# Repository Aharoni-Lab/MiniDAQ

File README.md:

# MiniDAQ
Simplified DAQ for Miniscopes and Minicams. This is effectively a smaller version of the [standard Miniscope DAQ](https://github.com/daharoni/Miniscope_DAQ_PCB) and does not include easily accessible trigger and sync connections but should support all other functionality of the Miniscope platform.

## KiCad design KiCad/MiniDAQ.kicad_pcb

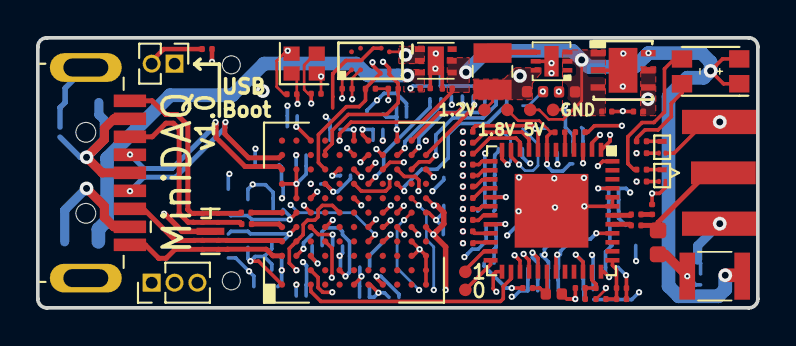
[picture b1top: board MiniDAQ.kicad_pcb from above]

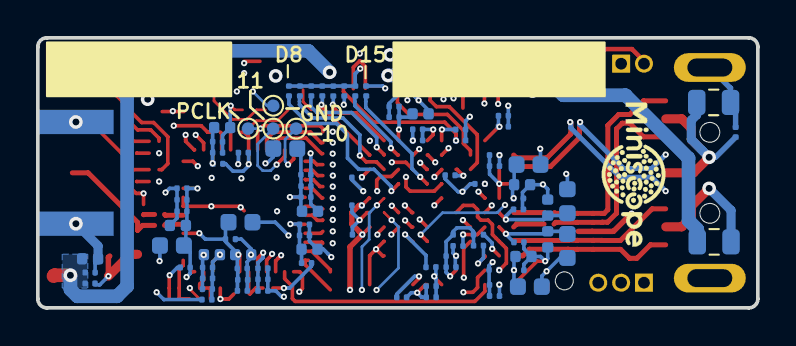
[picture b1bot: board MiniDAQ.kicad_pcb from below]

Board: 6 copper layers, 40.0 x 15.0 mm, 161 parts (93 on the bottom side), 96 nets.

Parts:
C1, C6, C9, C13, C14, C18, C19, C24, C25, C29, C38, C42, C49, C54, C60, C64, C66, C69, C71: 10nF; C_0201_0603Metric_L
C2, C5, C7, C10, C12, C15, C20, C23, C26, C30, C35, C37, C39, C40, C41, C43, C45, C46, C48, C50, C51, C53, C57, C58, C59, C61, C63, C65, C67, C68, C70, C72, C74: 0.1uF; C_0201_0603Metric_L
C3, C8, C11: 4.7uF; C_0402_1005Metric_L
C4, C22, C28, C32, C73, C75: 10uF; C_0402_1005Metric_L
C16, C21, C27, C31, C33, C34, C77, C78: 1uF; C_0201_0603Metric_L
C17: 47nF; C_0201_0603Metric_L
C36, C47, C52: 2.2uF; C_0402_1005Metric_L
C44, C62, C76: 22uF; C_0402_1005Metric_L
C55, C56: 12pF; C_0201_0603Metric_L
C79: 0 Res; C_0201_0603Metric_L
D1: LTST-C155GEKT; LED_4_P138_270X320X110L50X90N
J1: USB3_A; USB3_A_Plug_Wuerth_692112030100_Horizontal
J2: SMA-J-P-H-ST-EM1; SMA_Samtec_SMA-J-P-H-ST-EM1_EdgeMount
J3, J4, J5, J6: Conn_01x01; Conn_1x1_700_Circular_Pad
J7: Conn_01x03; PinHeader_1x03_P1.27mm_Vertical
JP1: Jumper_2_Open; PinHeader_1x02_P1.27mm_Vertical
J_NA: Conn_01x01; Conn_1x1_700_Circular_Pad
J_NA#2, J_NA#3, J_NA#4, J_NA#5, J_NA#6, J_NA#7, J_NA#8: Conn_01x01; Conn_1x1_700_Circular_Pad
L1, L2, L3, L5, L6, L8, L9, L10: BLM18PG471SN1D; L_0603_1608Metric_L
L4, L7: BLM21PG221SN1D; L_0805_2012Metric
L11: ADL3225V-470MT-TL000; L_1210_3225Metric_L
L12: LQM2HPN1R0MG0; L_1008_2520Metric_L
Q1, Q2: MMBT3904LP-7B; TRXDFN3_101X61X53L25X15N
R1, R2, R3, R9, R14, R15, R29, R43: 10K; R_0201_0603Metric_ERJ_L
R4, R6: 10K 1%; R_0201_0603Metric_ERJ_L
R5, R8: 0 1%; R_0201_0603Metric_ERJ_L
R7: 50; R_0201_0603Metric_ERJ_L
R10, R11: 2k; R_0201_0603Metric_ERJ_L
R12: 200 1%; R_0201_0603Metric_ERJ_L
R13: 6.04K 1%; R_0201_0603Metric_ERJ_L
R16, R17, R18, R19, R20, R21, R22, R23, R26, R27, R28, R33, R34, R35, R36, R37, R38, R39, R40: 22; R_0201_0603Metric_ERJ_L
R24, R25, R30, R31, R32: 2K; R_0201_0603Metric_ERJ_L
R41, R42: 0; R_0201_0603Metric_ERJ_L
U1: DS90UB934-Q1; QFN_49_P50_700X700X100L40X24T410N
U2: NCP360; SON7P65_200X200X55L30X30T160X90L
U3: SP3010-04UTG; uDFN-10
U4: CYUSB3014; BGA121CP80_11X11_1000X1000X120B30
U5: M24M02-R
U6: SC189CULTRT; SON_7P50_200X200X57L35X24T170X80N
U7: NCP692MN18T2G; NCP692MN50T2G
Y1: SMD_CRYSTAL; Crystal_SMD_2016-4Pin_2.0x1.6mm

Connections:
+1V2: C62.1, C63.1, C64.1, C65.1, C66.1, C67.1, C68.1, C69.1, C70.1, C71.1, C72.1, C76.1, J_NA#6.1, L5.1, L6.1, L8.1, L12.2, U4.B10, U4.C3, U4.E9, U4.F11, U4.H1, U4.J11, U4.L5, U4.L7, U6.6
+1V8: C13.2, C14.2, C15.2, C16.2, C37.1, C38.1, C41.1, C42.1, C48.1, C49.1, C53.1, C54.1, C58.1, C59.1, C60.1, C61.1, C78.1, J_NA#5.1, L1.1, L2.1, L3.1, L9.1, R1.1, R2.1, R3.1, R9.2, R14.1, R24.1, R25.1, R29.1, R40.1, R41.2, R42.2, R43.1, U1.7, U1.29, U4.B1, U4.C11, U4.E3, U4.F1, U4.H11, U4.L9, U5.A2, U7.4, U7.5
+5V: C34.1, C50.1, C73.1, C74.1, C75.1, C77.1, D1.1, D1.2, J_NA#3.1, L11.2, R30.2, U2.4, U2.5, U4.E11, U6.2, U6.3, U7.1, U7.3, U7.6
/Deserializer/COAX+: C12.2, J2.1, L10.1
/Deserializer/GPIO0: U1.28, U4.D4
/Deserializer/GPIO1: U1.27, U4.D5
/Deserializer/GPIO2: U1.26, U4.C1
/Deserializer/GPIO3: U1.25, U4.C2
/Deserializer/HSYNC: R27.1, U1.10
/Deserializer/I2C_SCL: R24.2, U1.2, U4.D9, U5.C1
/Deserializer/I2C_SDA: R25.2, U1.1, U4.D10, U5.D2
/Deserializer/IDX: C23.2, R6.2, R8.1, U1.35
/Deserializer/LOCK: U1.48, U4.K5
/Deserializer/MODE: C5.2, R4.2, R5.1, U1.37
/Deserializer/OEN: R2.2, U1.5
/Deserializer/OSS_SEL: R3.2, U1.4
/Deserializer/PCLK: J5.1, R26.1, U1.8
/Deserializer/PDB: C4.2, R1.2, U1.30
/Deserializer/ROUT0: J_NA#7.1, U1.24
/Deserializer/ROUT1: J_NA#8.1, U1.23
/Deserializer/ROUT2: R16.1, U1.22
/Deserializer/ROUT3: R17.1, U1.21
/Deserializer/ROUT4: R18.1, U1.19
/Deserializer/ROUT5: R19.1, U1.18
/Deserializer/ROUT6: R20.1, U1.16
/Deserializer/ROUT7: R21.1, U1.15
/Deserializer/ROUT8: R22.1, U1.14
/Deserializer/ROUT9: R23.1, U1.13
/Deserializer/ROUT10: J3.1, U1.12
/Deserializer/ROUT11: J4.1, U1.11
/Deserializer/VDD11_D: C6.2, C7.2, C8.2, R41.1, U1.3
/Deserializer/VDD11_DVP: C9.2, C10.2, C11.2, R42.1, U1.20
/Deserializer/VDD11_FPD: C1.2, C2.2, C3.2, C79.2, R9.1, U1.34
/Deserializer/VDD18: C29.2, C30.2, C31.2, C32.2, L3.2, R4.1, R6.1, U1.17
/Deserializer/VDD18_FPD0: C24.2, C25.2, C26.2, C27.2, C28.2, L2.2, U1.31, U1.40
/Deserializer/VDD18_P0: C18.2, C19.2, C20.2, C21.2, C22.2, L1.2, U1.36, U1.45
/Deserializer/VSYNC: R28.1, U1.9
/USB/AVDD: C35.1, C36.1, L5.2, U4.A7
/USB/CVDDQ: C51.1, C52.1, L9.2, U4.B6
/USB/FSLC0: R15.1, U4.B2, U4.B4, U4.E6
/USB/GPIO1: J7.2, U4.K7
/USB/GPIO2: J7.3, U4.K6
/USB/LOCK_OUT: R32.2, U4.H6
/USB/PMODE0: JP1.1, U4.G4
/USB/PMODE1: R29.2, U4.H4
/USB/RESET_IN: C57.1, R14.2, U4.C5
/USB/SSD_N: J1.2, U4.A10
/USB/SSD_P: J1.3, U4.A9
/USB/SS_RX_N: J1.8, U3.4, U3.7, U4.A4
/USB/SS_RX_P: J1.9, U3.5, U3.6, U4.A3
/USB/SS_TX_N: C39.2, J1.5, U3.1, U3.10
/USB/SS_TX_P: C40.2, J1.6, U3.2, U3.9
/USB/STATUS: R31.2, U4.G5
/USB/TX_N: C39.1, U4.A6
/USB/TX_P: C40.1, U4.A5
/USB/U3RXVDDQ: C43.1, C44.1, L6.2, U4.A2
/USB/U3TXVDDQ: C46.1, C47.1, L8.2, U4.B5
/USB/XTAL_IN: C56.1, U4.C6, Y1.1
/USB/XTAL_OUT: C55.1, U4.C7, Y1.3
GND: C1.1, C2.1, C3.1, C4.1, C5.1, C6.1, C7.1, C8.1, C9.1, C10.1, C11.1, C13.1, C14.1, C15.1, C16.1, C18.1, C19.1, C20.1, C21.1, C22.1, C23.1, C24.1, C25.1, C26.1, C27.1, C28.1, C29.1, C30.1, C31.1, C32.1, C33.2, C34.2, C35.2, C36.2, C37.2, C38.2, C41.2, C42.2, C43.2, C44.2, C45.1, C46.2, C47.2, C48.2, C49.2, C50.2, C51.2, C52.2, C53.2, C54.2, C55.2, C56.2, C57.2, C58.2, C59.2, C60.2, C61.2, C62.2, C63.2, C64.2, C65.2, C66.2, C67.2, C68.2, C69.2, C70.2, C71.2, C72.2, C73.2, C74.2, C75.2, C76.2, C77.2, C78.2, C79.1, J1.4, J1.7, J2.2, J6.1, J7.1, J_NA#4.1, L7.2, Q1.2, Q2.2, R5.2, R7.2, R8.2, R12.2, R13.2, R15.2, R33.1, R34.1, R35.1, R36.1, R37.1, R38.1, R39.1, U1.43, U1.44, U1.49, U2.1, U2.2, U2.7, U3.3, U3.8, U4.A1, U4.A8, U4.B7, U4.B8, U4.B9, U4.D8, U4.E2, U4.G1, U4.G11, U4.K3, U4.K4, U4.L1, U4.L2, U4.L3, U4.L6, U4.L11, U5.B2, U5.D3, U6.5, U6.7, U7.2, U7.7, Y1.2, Y1.4
unnamed: C12.1, U1.41
unnamed: C17.1, U1.42
unnamed: C17.2, R7.1
unnamed: C33.1, L4.2, U2.3
unnamed: C45.2, J1.10, L7.1
unnamed: D1.3, R11.1
unnamed: D1.4, R10.1
unnamed: J1.1, L4.1
unnamed: JP1.2, R43.2
unnamed: L10.2, L11.1, R30.1
unnamed: L12.1, U6.4
unnamed: Q1.1, R31.1
unnamed: Q1.3, R10.2
unnamed: Q2.1, R32.1
unnamed: Q2.3, R11.2
unnamed: R12.1, U4.B3
unnamed: R13.1, U4.C8
unnamed: R16.2, U4.F10
unnamed: R17.2, U4.F9
unnamed: R18.2, U4.F7
unnamed: R19.2, U4.G10
unnamed: R20.2, U4.G9
unnamed: R21.2, U4.F8
unnamed: R22.2, U4.H10
unnamed: R23.2, U4.H9
unnamed: R26.2, U4.J6
unnamed: R27.2, U4.J5
unnamed: R28.2, U4.H5
unnamed: R33.2, U4.J10
unnamed: R34.2, U4.J9
unnamed: R35.2, U4.K11
unnamed: R36.2, U4.L10
unnamed: R37.2, U4.K10
unnamed: R38.2, U4.K9
unnamed: R39.2, U4.J8
unnamed: R40.2, U4.G8

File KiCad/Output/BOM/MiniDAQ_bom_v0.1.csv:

Component,Description,Part,References,Value,Footprint,Quantity Per PCB,Datasheet,Part Number,Note,Size
1,"Unpolarized capacitor, small symbol",C_Small,C79,0 Res,C_0201_0603Metric_L,1,~,ERJ-1GN0R00C,,
2,"Unpolarized capacitor, small symbol",C_Small,C2 C5 C7 C10 C12 C15 C20 C23 C26 C30 C35 C37 C39 C40 C41 C43 C45 C46 C48 C50 C51 C53 C57 C58 C59 C61 C63 C65 C67 C68 C70 C72 C74,0.1uF,C_0201_0603Metric_L,33,~,CC0201KRX5R6BB104,,
3,"Unpolarized capacitor, small symbol",C_Small,C1 C6 C9 C13 C14 C18 C19 C24 C25 C29 C38 C42 C49 C54 C60 C64 C66 C69 C71,10nF,C_0201_0603Metric_L,19,~,CC0201KRX7R7BB103,,
4,"Unpolarized capacitor, small symbol",C_Small,C4 C22 C28 C32 C73 C75,10uF,C_0402_1005Metric_L,6,~,CC0402MRX5R5BB106,,
5,"Unpolarized capacitor, small symbol",C_Small,C55 C56,12pF,C_0201_0603Metric_L,2,~,CC0201JRNPO8BN120,,
6,"Unpolarized capacitor, small symbol",C_Small,C16 C21 C27 C31 C33 C34 C77 C78,1uF,C_0201_0603Metric_L,8,~,CC0201MRX5R5BB105,,
7,"Unpolarized capacitor, small symbol",C_Small,C36 C47 C52,2.2uF,C_0402_1005Metric_L,3,~,CC0402MRX5R6BB225,,
8,"Unpolarized capacitor, small symbol",C_Small,C44 C62 C76,22uF,C_0402_1005Metric_L,3,~,CL05A226MQ5N6J8,,
9,"Unpolarized capacitor, small symbol",C_Small,C3 C8 C11,4.7uF,C_0402_1005Metric_L,3,~,CC0402MRX5R6BB475,,
10,"Unpolarized capacitor, small symbol",C_Small,C17,47nF,C_0201_0603Metric_L,1,~,CC0201KRX5R5BB473,,
11,"Dual LED, cathodes on pins 3 and 4",LTST-C155GEKT,D1,LTST-C155GEKT,LED_4_P138_270X320X110L50X90N,1,https://media.digikey.com/pdf/Data%20Sheets/Lite-On%20PDFs/L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,LTST-C155GEKT,,
15,USB 3.0 A connector,USB3_A,J1,USB3_A,USB3_A_Plug_Wuerth_692112030100_Horizontal,1,~,6.92112E+11,,
17,FIXED IND 47UH 500MA 900 MOHM,ADL3225V-470MT-TL000,L11,ADL3225V-470MT-TL000,L_1210_3225Metric_L,1,https://product.tdk.com/info/en/catalog/datasheets/inductor_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,ADL3225V-470MT-TL000,47uH,1210
18,FERRITE BEAD 470 OHM 0603 1LN,BLM18PG471SN1D,L1 L2 L3 L5 L6 L8 L9 L10,BLM18PG471SN1D,L_0603_1608Metric_L,8,https://www.murata.com/en-us/products/productdata/8796738650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,BLM18PG471SN1D,470 Ohms @ 100MHz,603
19,"Inductor, small symbol",L_Small,L4 L7,BLM21PG221SN1D,L_0805_2012Metric,2,https://www.murata.com/en-us/products/en-us/products/product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,BLM21PG221SN1D,,
20,"Inductor, small symbol",L_Small,L12,LQM2HPN1R0MG0,L_1008_2520Metric_L,1,https://www.mouser.com/datasheet/2/281/JELF243B-0019-1634195.pdf,LQM2HPN1R0MG0,,
21,TRANS NPN 40V 0.2A DFN1006-3,MMBT3904LP-7B,Q1 Q2,MMBT3904LP-7B,TRXDFN3_101X61X53L25X15N,2,https://www.diodes.com/assets/Datasheets/ds31835.pdf,MMBT3904LP-7B,,
22,"Resistor, small US symbol",R_Small_US,R41 R42,0,R_0201_0603Metric_ERJ_L,2,~,ERJ-1GN0R00C,,
23,"Resistor, small US symbol",R_Small_US,R5 R8,0 1%,R_0201_0603Metric_ERJ_L,2,~,ERJ-1GN0R00C,,
24,"Resistor, small US symbol",R_Small_US,R1 R2 R3 R9 R14 R15 R29 R43,10K,R_0201_0603Metric_ERJ_L,8,~,ERJ-1GNF1002C,,
25,"Resistor, small US symbol",R_Small_US,R4 R6,10K 1%,R_0201_0603Metric_ERJ_L,2,~,ERJ-1GNF1002C,,
26,"Resistor, small US symbol",R_Small_US,R12,200 1%,R_0201_0603Metric_ERJ_L,1,~,ERJ-1GEF2000C,,
27,"Resistor, small US symbol",R_Small_US,R16 R17 R18 R19 R20 R21 R22 R23 R26 R27 R28 R33 R34 R35 R36 R37 R38 R39 R40,22,R_0201_0603Metric_ERJ_L,19,~,ERJ-1GNF22R0C,,
28,"Resistor, small US symbol",R_Small_US,R10 R11 R24 R25 R30 R31 R32,2k,R_0201_0603Metric_ERJ_L,7,~,ERJ-1GNF2001C,,
29,"Resistor, small US symbol",R_Small_US,R7,50,R_0201_0603Metric_ERJ_L,1,~,ERJ-1GNF49R9C,,
30,"Resistor, small US symbol",R_Small_US,R13,6.04K 1%,R_0201_0603Metric_ERJ_L,1,~,ERJ-1GNF6041C,,
31,EZ-USB® FX3:SuperSpeed USB Controller,CYUSB3014,U4,CYUSB3014,BGA121CP80_11X11_1000X1000X120B30,1,https://www.cypress.com/file/140296/download,CYUSB3014-BZXC,,
32,IC DESERIALIZER 12 BIT 48-VQFN,DS90UB934-Q1,U1,DS90UB934-Q1,QFN_49_P50_700X700X100L40X24T410N,1,http://www.ti.com/lit/ds/symlink/ds90ub934-q1.pdf,DS90UB914ATRHSJQ1,,
33,2-Mbit serial I²C bus EEPROM,M24M02-R,U5,M24M02-R,M24M02-R,1,https://www.st.com/content/ccc/resource/technical/document/d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,M24M02-DRCS6TP/K,,
34,USB Positive Overvoltage,NCP360,U2,NCP360,SON7P65_200X200X55L30X30T160X90L,1,https://www.onsemi.com/pub/Collateral/NCP360-D.PDF,NCP360MUTBG,,
35,,NCP690MN50T2G(5V),U7,NCP692MN18T2G,NCP692MN50T2G,1,https://www.onsemi.com/pub/Collateral/NCP690-D.PDF,NCP692MN18T2G,,
36,"2.5MHz, 1.5A Synchronous Step Down Regulator",SC189xULTRT,U6,SC189CULTRT,SON_7P50_200X200X57L35X24T170X80N,1,https://www.mouser.com/datasheet/2/761/sc189-1366204.pdf,SC189CULTRT,,
37,TVS Diode Array,SP3010-04UTG,U3,SP3010-04UTG,uDFN-10,1,https://www.littelfuse.com/~/media/electronics/datasheets/tv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,SP3010-04UTG,,
38,2.5mm x 2mm,SMD_CRYSTAL,Y1,SMD_CRYSTAL,Crystal_SMD_2016-4Pin_2.0x1.6mm,1,,CX2016DB19200H0FLJC2,,
,,,,,,,,,,
,,,,,,,,,,
,,,,,,,,,,
,,,,,,,,,,
,,,,,,,,,,
Component Groups:,38,,,,,,,,,
Component Count:,153,,,,,,,,,
Fitted Components:,153,,,,,,,,,
Number of PCBs:,1,,,,,,,,,
Total components:,153,,,,,,,,,
Schematic Version:,v0.1,,,,,,,,,
Schematic Date:,7/15/2020,,,,,,,,,
PCB Variant:,[u'default'],,,,,,,,,
BoM Date:,7/15/2020 22:13,,,,,,,,,
Schematic Source:,C:\Users\DBAharoni\Documents\Projects\MiniDAQ\KiCad\MiniDAQ.sch,,,,,,,,,
KiCad Version:,Eeschema (5.1.5)-3,,,,,,,,,

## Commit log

2020-07-10 Create KiCad project for MiniDAQ
2020-07-11 Add initial schematic layout and some initial components
2020-07-11 Layout initial schematic of deserializer
2020-07-12 Layout schematic for the most part. Needs to be fully reviewed.
2020-07-13 1.8 Voltage regulator added, minor fixes to the schematic
    - Added the NCP690MN18T2G 5V to 1.8 Volt voltage regulator
    - Checked the connections in the PCB
    - Added annotation on the deserializer output
2020-07-13 Update 1.8V LDO and change USB3 micro-B connector
2020-07-13 Hierarchical power pins added
    - Added the 1V8, 1V2 and 5V pins to connect the sheets one to each other
    - Slightly modified the main sheet to make the connections clear
2020-07-13 Remove global power sheet labels. Switch USB connector to type A
2020-07-13 Annotate all components.
2020-07-13 Update footprint of all components and switch many to 0201s
2020-07-14 Update footprints and add 3D models to all comoponents. Ready for layout + routing.
2020-07-14 Correct USB to CYUSB3014 connections. I HOPE THIS IS CORRECT!
2020-07-15 Route PCB. 1.2V and final 5V connection left. Then adding headers
2020-07-16 All files for v0.1 fab and assembly through PCBway
2020-09-02 Minor changes and added test pads for possible v1.0 of MiniDAQ
2020-09-02 Update rev on schematic sheets.
2020-09-09 Update v1.0 gerbers and generate .step file.
2022-06-14 Addes Body Parts
    - Added STL files for the bottom and top shell

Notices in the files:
parts and their libraries:
Copyright 2016 Accelerated Designs. All rights reserved.
